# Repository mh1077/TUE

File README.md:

# TUE
Tochteruhrempfänger für MRClock

Dieser Empfänger verarbeitet die Multicast Telegramme eines MRClock Zeitzeichenservers. Aus einer LiPo Zelle (4.2 V) werden die 12 Volt bzw. 24 Volt für die Tochteruhren, auch Nebenuhren genannt, generiert und gleichzeitig der Empfänger (ESP8266) versorgt. Eine Ladeschaltung läd aus einer 5V Versorgung (USB oder Steckernetzteil) die LiPo Zelle.  

Eine Abschaltung bei niedriger LiPo Zellenspannung (ab ca. 3.1V) ist eingebaut. Der Empfänger behält die an der Tochteruhr angezeigte Uhrzeit gespeichert und läuft während dem Ladevorgang ab ca. 3.6V wieder los.

Ein TUE kann auch die Normalzeit mit NTP empfangen. Das funktioniert so. Wird ca. 6 Minuten nach der Konfiguration des Empfängers kein gültiges MRClock Telegramm empfangen, wird die Normalzeit angezeigt. Die Normalzeit wird auch angezeigt, wenn 24 Stunden kein gültiges MRClock Telegramm empfangen wurde. Es wird die MEZ mit automatischer Sommer-/Winterzeitumstellung angezeigt. Wird der Empfänger neu gestartet, sei es durch Reset oder Einschalten, wird nach ca. 6 Minuten auf NTP umgestellt wenn kein MRClock Telegramm empfangen wurde.

Das Projekt enthält die EAGLE Dateien, den Arduino Sourcecode und eine Bedienungsanleitung für den Tochteruhrempfänger.

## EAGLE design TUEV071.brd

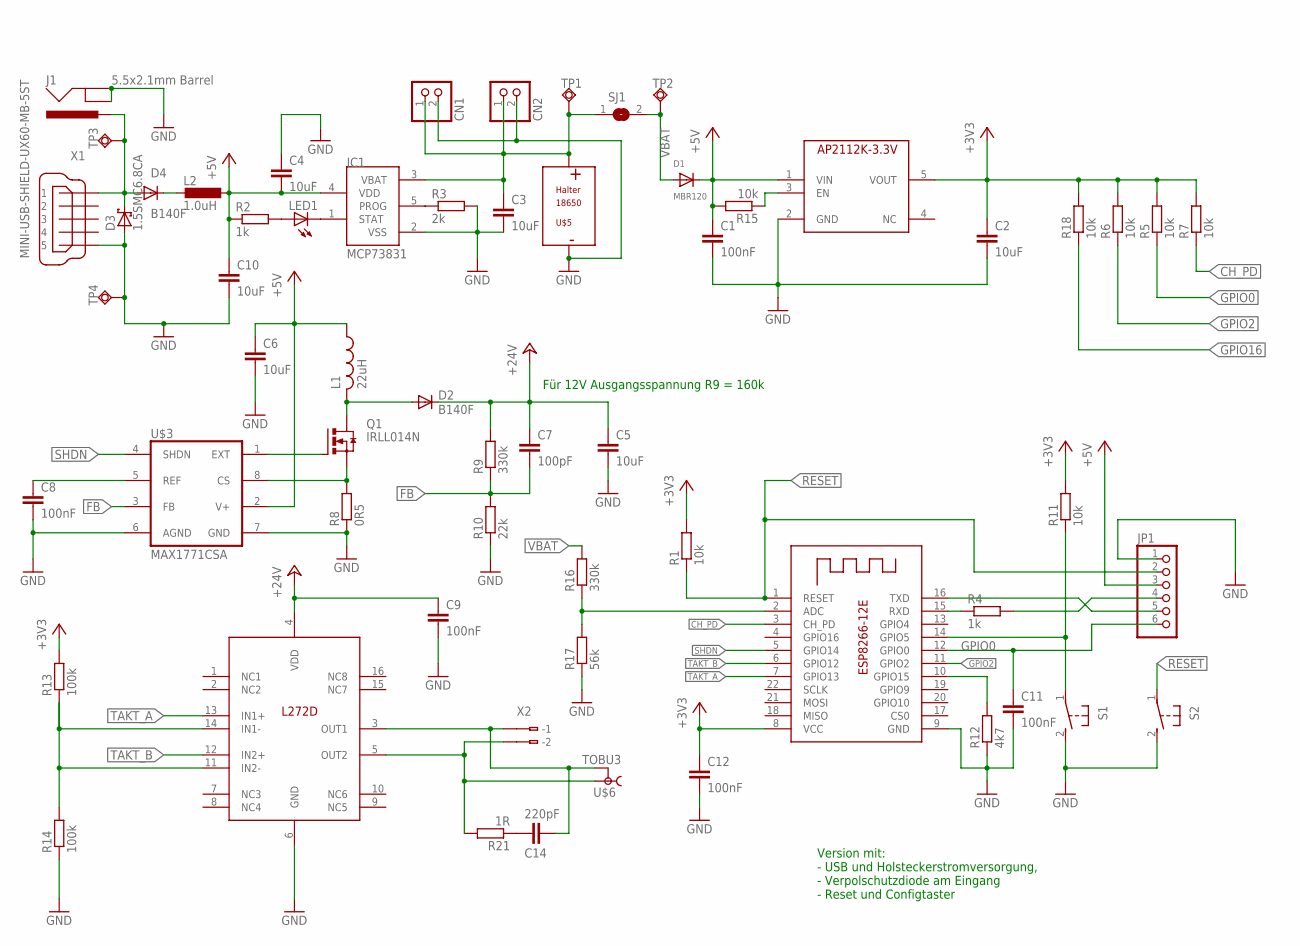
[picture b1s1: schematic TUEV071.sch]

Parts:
C1, C8, C9, C11, C12: 100nF; C0603K
C2, C3, C4, C6, C10: 10uF; C0603K
C5: 10uF; C1210K
C7: 100pF; C0603K
C14: 220pF; C0603K
CN1, CN2: JST_2PIN-SMT-RA; JST-PH-2-SMT-RA
D1: MBR120; SOD-123
D2, D4: B140F; DO214AC
D3: 1.5SMC6.8CA; SMC
IC1: MCP73831; SOT23-5L
J1: 5.5x2.1mm Barrel; POWER_JACK_SMD
JP1: PINHD-1X6; 1X06
L1: 22uH; L5650M
L2: 1.0uH; L3230M
LED1: LEDCHIPLED_0805; CHIPLED_0805
Q1: IRLL014N; SOT223
R1, R5, R6, R7, R11, R15, R18: 10k; M1206
R2, R4: 1k; M1206
R3: 2k; M1206
R8: 0R5; R2512
R9, R16: 330k; M1206
R10: 22k; M1206
R12: 4k7; M1206
R13, R14: 100k; M1206
R17: 56k; M1206
R21: 1R; M1206
S1, S2: 31-XX; B3F-31XX
SJ1: SJ
TP1, TP2, TP3, TP4: TPSQPAD1-13Y; P1-13Y
U$1: AP2112-3.3; SOT23-5L
U$2: L272D; SO16
U$3: MAX1771CSA; SO08
U$4: ESP-12E
U$5: HA1X18650SMD
U$6: TOBU3; TOBU3-REICHELT
X1: MINI-USB-SHIELD-UX60-MB-5ST; UX60-MB-5ST
X2: 233-102

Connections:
+3V3: C2.1, C12.1, R1.2, R5.2, R6.2, R7.2, R11.2, R13.2, R18.2, U$1.5 (VOUT), U$4.8 (VCC)
+5V: C1.1, C4.2, C6.1, C10.1, D1.C, IC1.4 (VDD), JP1.3, L1.1, L2.1, R2.1, R15.2, U$1.1 (VIN), U$3.2 (V+)
+24V: C5.1, C7.1, C9.1, D2.C, R9.2, U$2.4 (VDD)
CH_PD: R7.1, U$4.3 (CH_PD)
FB: C7.2, R9.1, R10.2, U$3.3 (FB)
GND: C1.2, C2.2, C3.2, C4.1, C5.2, C6.2, C8.2, C9.2, C10.2, C11.2, C12.2, CN1.2 (1), CN2.2 (1), D3.A, IC1.2 (VSS), J1.GND (GNDBREAK), J1.P$4 (GND), JP1.1, R3.2, R8.1, R10.1, R12.1, R14.1, R17.1, S1.2 (S), S2.2 (S), TP4.TP, U$1.2 (GND), U$2.6 (GND), U$3.6 (AGND), U$3.7 (GND), U$4.9 (GND), U$5.P$2-, X1.5
GPIO0: C11.1, JP1.6, R5.1, U$4.12 (GPIO0)
GPIO2: R6.1, U$4.11 (GPIO2)
GPIO16: R18.1
unnamed: JP1.5, U$4.16 (TXD)
unnamed: JP1.4, R4.2
unnamed: R4.1, U$4.15 (RXD)
unnamed: IC1.1 (STAT), LED1.C
unnamed: LED1.A, R2.2
unnamed: IC1.5 (PROG), R3.1
unnamed: Q1.1 (G), U$3.1 (EXT)
unnamed: D4.C, L2.2
unnamed: Q1.3 (S), R8.2, U$3.8 (CS)
unnamed: D2.A, L1.2, Q1.2 (D), Q1.4 (D)
unnamed: C14.2, U$2.3 (OUT1), U$6.2, U$6.2@1 (2), U$6.2@2 (2), X2.B1 (B-1)
unnamed: C8.1, U$3.5 (REF)
unnamed: R21.2, U$2.5 (OUT2), U$6.1, X2.B2 (B-2)
unnamed: R12.2, U$4.10 (GPIO15)
unnamed: D3.C, D4.A, J1.VIN0 (PWR), TP3.TP, X1.1
unnamed: R16.1, R17.2, U$4.2 (ADC)
unnamed: R15.1, U$1.3 (EN)
unnamed: C14.1, R21.1
unnamed: R11.1, S1.1, U$4.14 (GPIO5)
unnamed: R13.1, R14.2, U$2.11 (IN2-), U$2.14 (IN1-)
RESET: JP1.2, R1.1, S2.1, U$4.1 (RESET)
SHDN: U$3.4 (SHDN), U$4.5 (GPIO14)
TAKT_A: U$2.13 (IN1+), U$4.7 (GPIO13)
TAKT_B: U$2.12 (IN2+), U$4.6 (GPIO12)
VBAT: D1.A, R16.2, SJ1.2, TP2.TP
VBAT1: C3.1, CN1.1 (2), CN2.1 (2), IC1.3 (VBAT), SJ1.1, TP1.TP, U$5.P$1+

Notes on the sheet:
Für 12V Ausgangsspannung R9 = 160k
Version mit: - USB und Holsteckerstromversorgung, - Verpolschutzdiode am Eingang - Reset und Configtaster

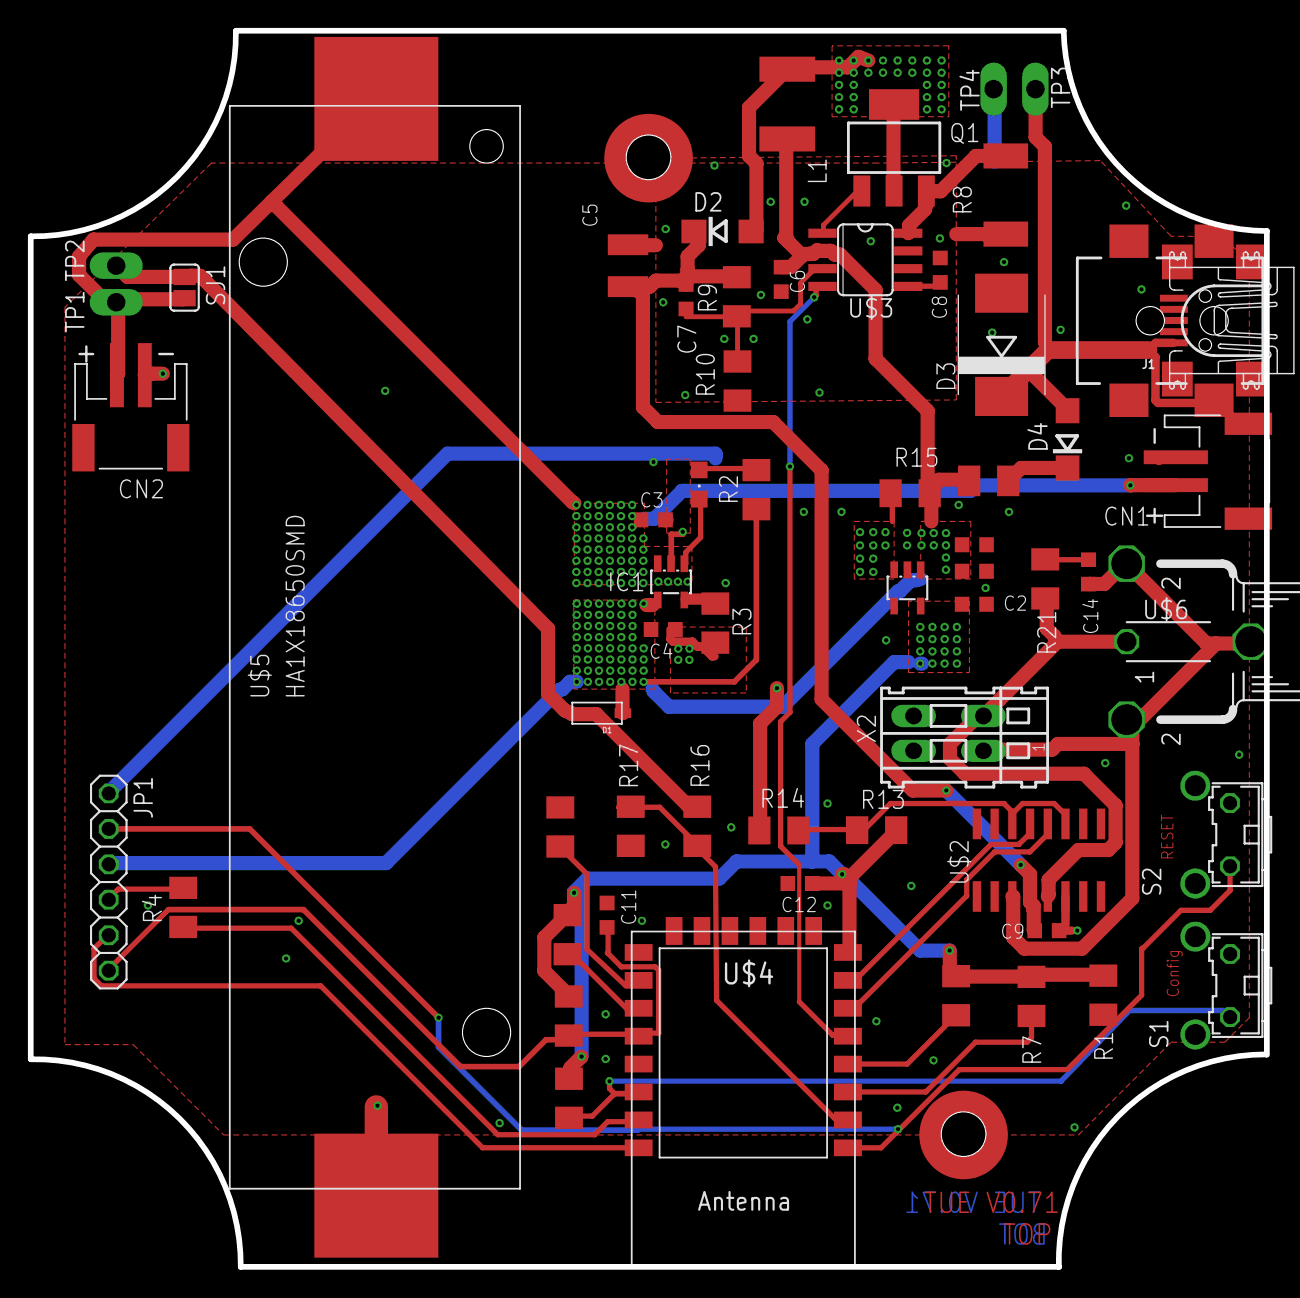
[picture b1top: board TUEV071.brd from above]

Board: 2 copper layers, 88.6 x 88.6 mm, 60 parts (0 on the bottom side), 34 nets.

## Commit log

2017-08-16 Create TUE_V1.3
    Freigegeben 16. August 2017 / Hoe
2017-08-16 Add files via upload
    Eagle Dateien für die Leiterplatte, eingepasst in ein FIBOX Gehäuse ABS oder PC 95/35 LT
2019-09-18 Add files via upload
    Bauteileliste
2019-09-22 Update Partlist_TUEV71

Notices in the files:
parts and their libraries:
SparkFun-Connectors: Licensing: Creative Commons ShareAlike 4.0 International - https://creativecommons.org/licenses/by-sa/4.0
